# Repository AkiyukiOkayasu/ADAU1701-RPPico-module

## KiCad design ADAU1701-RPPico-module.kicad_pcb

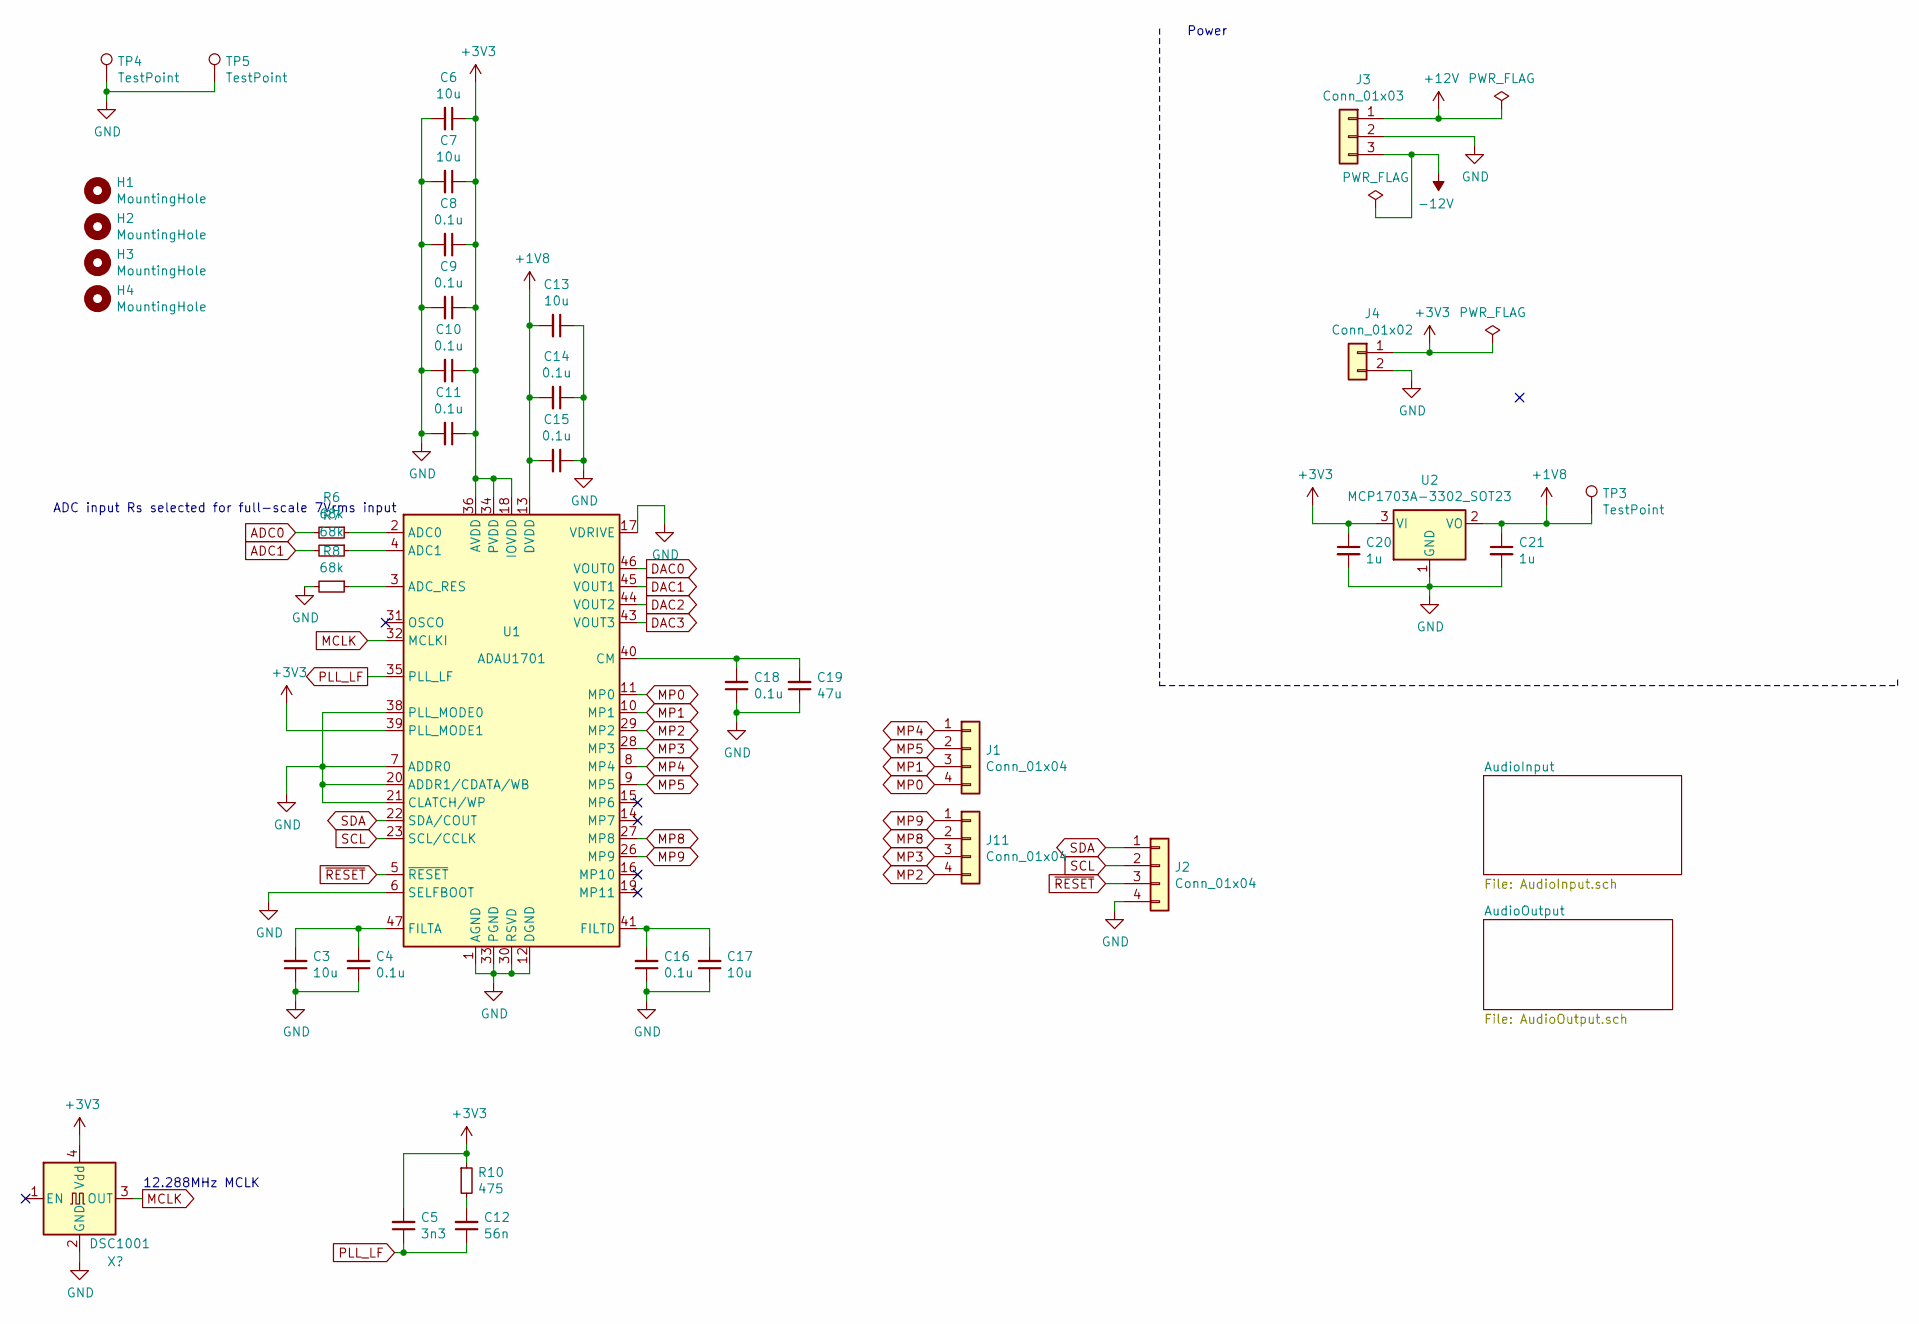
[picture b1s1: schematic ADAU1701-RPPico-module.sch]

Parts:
C3, C6, C7, C13, C17: 10u; C_0805_2012Metric_Pad1.18x1.45mm_HandSolder
C4, C8, C9, C10, C11, C14, C15, C16, C18: 0.1u; C_0402_1005Metric_Pad0.74x0.62mm_HandSolder
C5: 3n3; C_0603_1608Metric_Pad1.08x0.95mm_HandSolder
C12: 56n; C_0603_1608Metric_Pad1.08x0.95mm_HandSolder
C19: 47u; C_0805_2012Metric_Pad1.18x1.45mm_HandSolder
C20, C21: 1u; C_0603_1608Metric_Pad1.08x0.95mm_HandSolder
H1, H2, H3, H4: MountingHole; MountingHole_3.2mm_M3
J1, J11: Conn_01x04; PinHeader_1x04_P2.00mm_Vertical
J2: Conn_01x04; PinHeader_1x04_P2.54mm_Vertical
J3: Conn_01x03; PhoenixContact_MSTBA_2,5_3-G-5,08_1x03_P5.08mm_Horizontal
J4: Conn_01x02; PhoenixContact_MSTBA_2,5_2-G-5,08_1x02_P5.08mm_Horizontal
R6, R7, R8: 68k; R_0603_1608Metric_Pad0.98x0.95mm_HandSolder
R10: 475; R_0603_1608Metric_Pad0.98x0.95mm_HandSolder
TP3: TestPoint; TestPin_1.0SMD
TP4, TP5: TestPoint; TestPin_0.8THT
U1: ADAU1701; LQFP-48_7x7mm_P0.5mm
U2: MCP1703A-3302_SOT23; SOT-23

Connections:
+1V8: C13.2, C14.2, C15.2, C21.1, TP3.1, U1.13 (DVDD), U1.24 (DVDD), U2.2 (VO)
+3V3: C5.2, C6.1, C7.1, C8.1, C9.1, C10.1, C11.1, C20.1, J4.1, R10.1, U1.18 (IOVDD), U1.34 (PVDD), U1.36 (AVDD), U1.39 (PLL_MODE1), U1.48 (AVDD), U2.3 (VI)
+12V: J3.1; also elsewhere on the board
-12V: J3.3; also elsewhere on the board
ADC0: R6.2; also elsewhere on the board
ADC1: R7.2; also elsewhere on the board
DAC0: U1.46 (VOUT0); also elsewhere on the board
DAC1: U1.45 (VOUT1); also elsewhere on the board
DAC2: U1.44 (VOUT2); also elsewhere on the board
DAC3: U1.43 (VOUT3); also elsewhere on the board
GND: C3.1, C4.1, C6.2, C7.2, C8.2, C9.2, C10.2, C11.2, C13.1, C14.1, C15.1, C16.1, C17.1, C18.1, C19.1, C20.2, C21.2, J2.4, J3.2, J4.2, R8.2, TP4.1, TP5.1, U1.1 (AGND), U1.6 (SELFBOOT), U1.7 (ADDR0), U1.12 (DGND), U1.17 (VDRIVE), U1.20 (ADDR1/CDATA/WB), U1.21 (CLATCH/WP), U1.25 (DGND), U1.30 (RSVD), U1.33 (PGND), U1.37 (AGND), U1.38 (PLL_MODE0), U1.42 (AGND), U2.1 (GND); also elsewhere on the board
MP0: J1.4, U1.11 (MP0)
MP1: J1.3, U1.10 (MP1)
MP2: J11.4, U1.29 (MP2)
MP3: J11.3, U1.28 (MP3)
MP4: J1.1, U1.8 (MP4)
MP5: J1.2, U1.9 (MP5)
MP8: J11.2, U1.27 (MP8)
MP9: J11.1, U1.26 (MP9)
unnamed 20: U1.32 (MCLKI); also elsewhere on the board
unnamed: C3.2, C4.2, U1.47 (FILTA)
unnamed: C12.2, R10.2
unnamed: C16.2, C17.2, U1.41 (FILTD)
unnamed: C18.2, C19.2, U1.40 (CM)
unnamed 47: U1.31 (OSCO); also elsewhere on the board
unnamed: R6.1, U1.2 (ADC0)
unnamed: R7.1, U1.4 (ADC1)
unnamed: R8.1, U1.3 (ADC_RES)
PLL_LF: C5.1, C12.1, U1.35 (PLL_LF)
SCL: J2.2, U1.23 (SCL/CCLK)
SDA: J2.1, U1.22 (SDA/COUT)
~RESET: J2.3, U1.5 (~RESET)

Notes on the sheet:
ADC input Rs selected for full-scale 7Vrms input
Power
12.288MHz MCLK

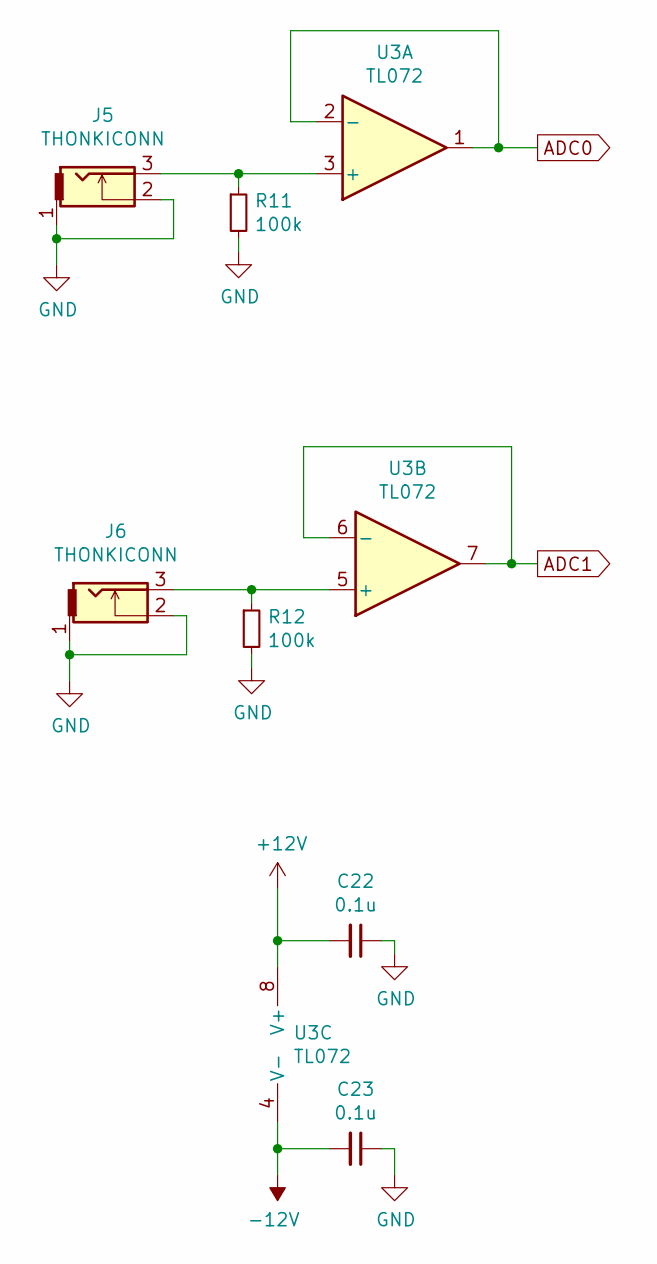
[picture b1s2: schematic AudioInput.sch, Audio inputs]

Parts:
C22, C23: 0.1u; C_0603_1608Metric_Pad1.08x0.95mm_HandSolder
J5, J6: THONKICONN
R11, R12: 100k; R_0603_1608Metric_Pad0.98x0.95mm_HandSolder
U3: TL072; SOIC-8_3.9x4.9mm_P1.27mm

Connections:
+12V: C22.2, U3.8 (V+); also elsewhere on the board
-12V: C23.2, U3.4 (V-); also elsewhere on the board
ADC0: U3.1, U3.2 (-); also elsewhere on the board
ADC1: U3.6 (-), U3.7; also elsewhere on the board
GND: C22.1, C23.1, J5.1, J5.2, J6.1, J6.2, R11.2, R12.2; also elsewhere on the board
unnamed: J5.3, R11.1, U3.3 (+)
unnamed: J6.3, R12.1, U3.5 (+)

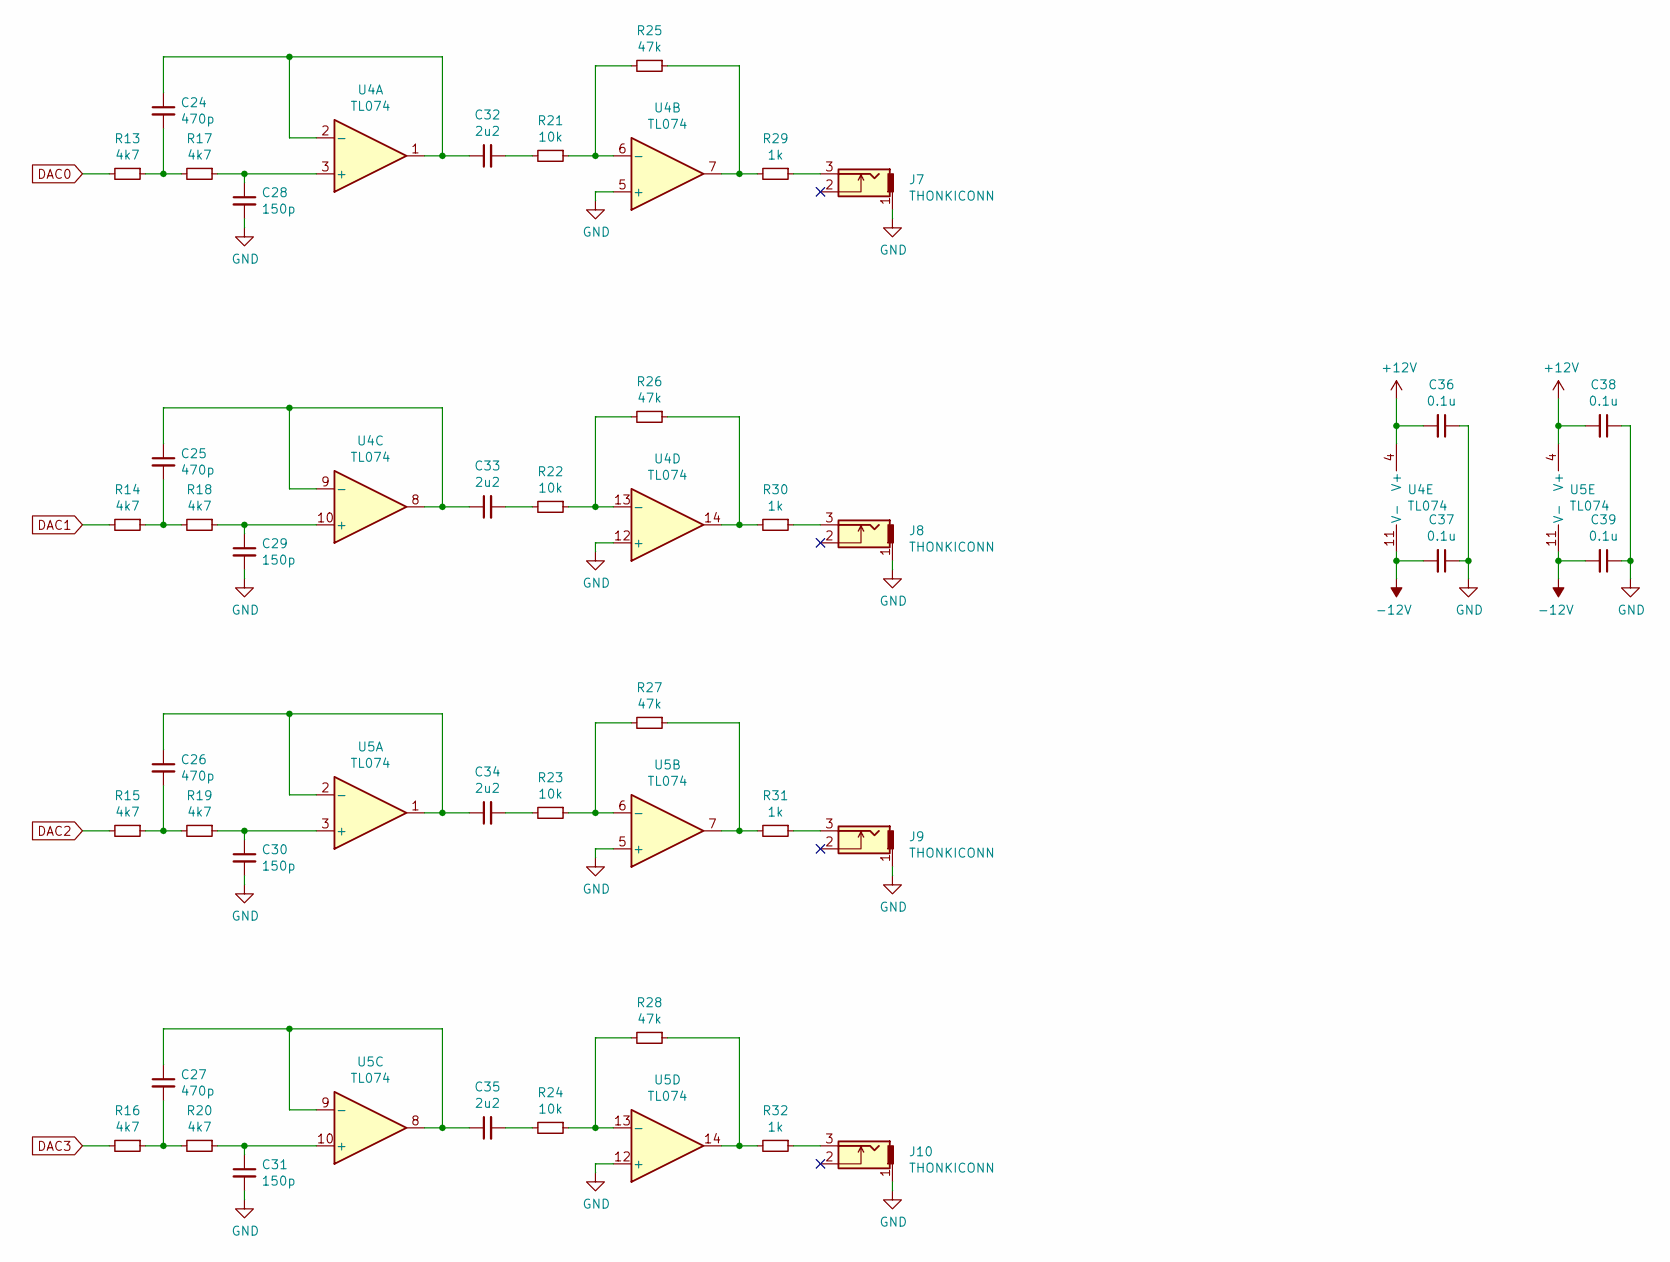
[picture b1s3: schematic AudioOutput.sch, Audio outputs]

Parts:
C24, C25, C26, C27: 470p; C_0603_1608Metric_Pad1.08x0.95mm_HandSolder
C28, C29, C30, C31: 150p; C_0603_1608Metric_Pad1.08x0.95mm_HandSolder
C32, C33, C34, C35: 2u2; C_1210_3225Metric_Pad1.33x2.70mm_HandSolder
C36, C37, C38, C39: 0.1u; C_0603_1608Metric_Pad1.08x0.95mm_HandSolder
J7, J8, J9, J10: THONKICONN
R13, R14, R15, R16, R17, R18, R19, R20: 4k7; R_0603_1608Metric_Pad0.98x0.95mm_HandSolder
R21, R22, R23, R24: 10k; R_0603_1608Metric_Pad0.98x0.95mm_HandSolder
R25, R26, R27, R28: 47k; R_0603_1608Metric_Pad0.98x0.95mm_HandSolder
R29, R30, R31, R32: 1k; R_0603_1608Metric_Pad0.98x0.95mm_HandSolder
U4, U5: TL074; SOIC-14_3.9x8.7mm_P1.27mm

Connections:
+12V: C36.2, C38.2, U4.4 (V+), U5.4 (V+); also elsewhere on the board
-12V: C37.2, C39.2, U4.11 (V-), U5.11 (V-); also elsewhere on the board
DAC0: R13.2; also elsewhere on the board
DAC1: R14.2; also elsewhere on the board
DAC2: R15.2; also elsewhere on the board
DAC3: R16.2; also elsewhere on the board
GND: C28.2, C29.2, C30.2, C31.2, C36.1, C37.1, C38.1, C39.1, J7.1, J8.1, J9.1, J10.1, U4.5 (+), U4.12 (+), U5.5 (+), U5.12 (+); also elsewhere on the board
unnamed: C24.1, C32.1, U4.1, U4.2 (-)
unnamed: C24.2, R13.1, R17.2
unnamed: C25.1, C33.1, U4.8, U4.9 (-)
unnamed: C25.2, R14.1, R18.2
unnamed: C26.1, C34.1, U5.1, U5.2 (-)
unnamed: C26.2, R15.1, R19.2
unnamed: C27.1, C35.1, U5.8, U5.9 (-)
unnamed: C27.2, R16.1, R20.2
unnamed: C28.1, R17.1, U4.3 (+)
unnamed: C29.1, R18.1, U4.10 (+)
unnamed: C30.1, R19.1, U5.3 (+)
unnamed: C31.1, R20.1, U5.10 (+)
unnamed: C32.2, R21.2
unnamed: C33.2, R22.2
unnamed: C34.2, R23.2
unnamed: C35.2, R24.2
unnamed: J7.3, R29.1
unnamed: J8.3, R30.1
unnamed: J9.3, R31.1
unnamed: J10.3, R32.1
unnamed: R21.1, R25.2, U4.6 (-)
unnamed: R22.1, R26.2, U4.13 (-)
unnamed: R23.1, R27.2, U5.6 (-)
unnamed: R24.1, R28.2, U5.13 (-)
unnamed: R25.1, R29.2, U4.7
unnamed: R26.1, R30.2, U4.14
unnamed: R27.1, R31.2, U5.7
unnamed: R28.1, R32.2, U5.14

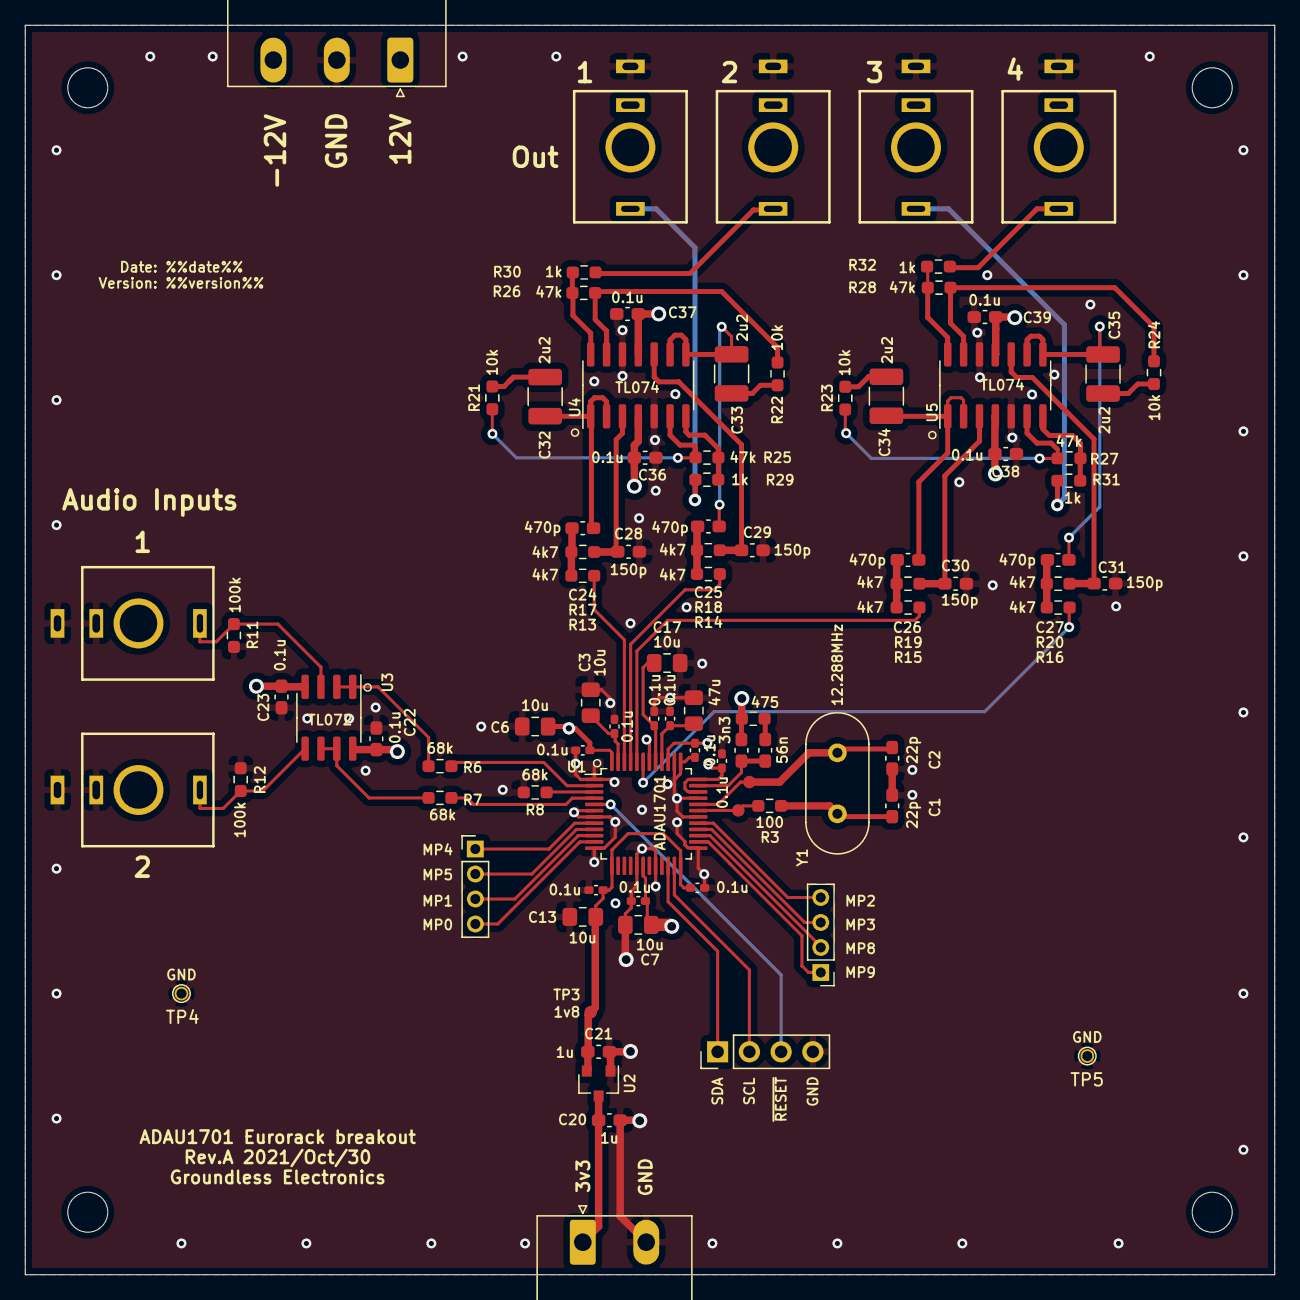
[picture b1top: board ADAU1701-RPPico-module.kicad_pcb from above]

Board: 4 copper layers, 100.0 x 100.0 mm, 92 parts (0 on the bottom side), 63 nets.

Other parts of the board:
C1, C2: 22p; C_0603_1608Metric_Pad1.08x0.95mm_HandSolder
R3: 100; R_0603_1608Metric_Pad0.98x0.95mm_HandSolder
TP1, TP2: TestPoint; TestPin_1.0SMD
Y1: 12.288MHz; Crystal_HC49-U_Vertical

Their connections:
GND: C1.2, C2.2; also elsewhere on the board
unnamed: C1.1, R3.2, Y1.1
unnamed 20: C2.1, TP1.1, Y1.2; also elsewhere on the board
unnamed 47: R3.1, TP2.1; also elsewhere on the board

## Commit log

2021-11-30 Update gitignore
2021-11-30 Add kicad files
2021-12-01 date and version
2022-01-20 Rev. B
2022-01-20 gitignore *.zip
